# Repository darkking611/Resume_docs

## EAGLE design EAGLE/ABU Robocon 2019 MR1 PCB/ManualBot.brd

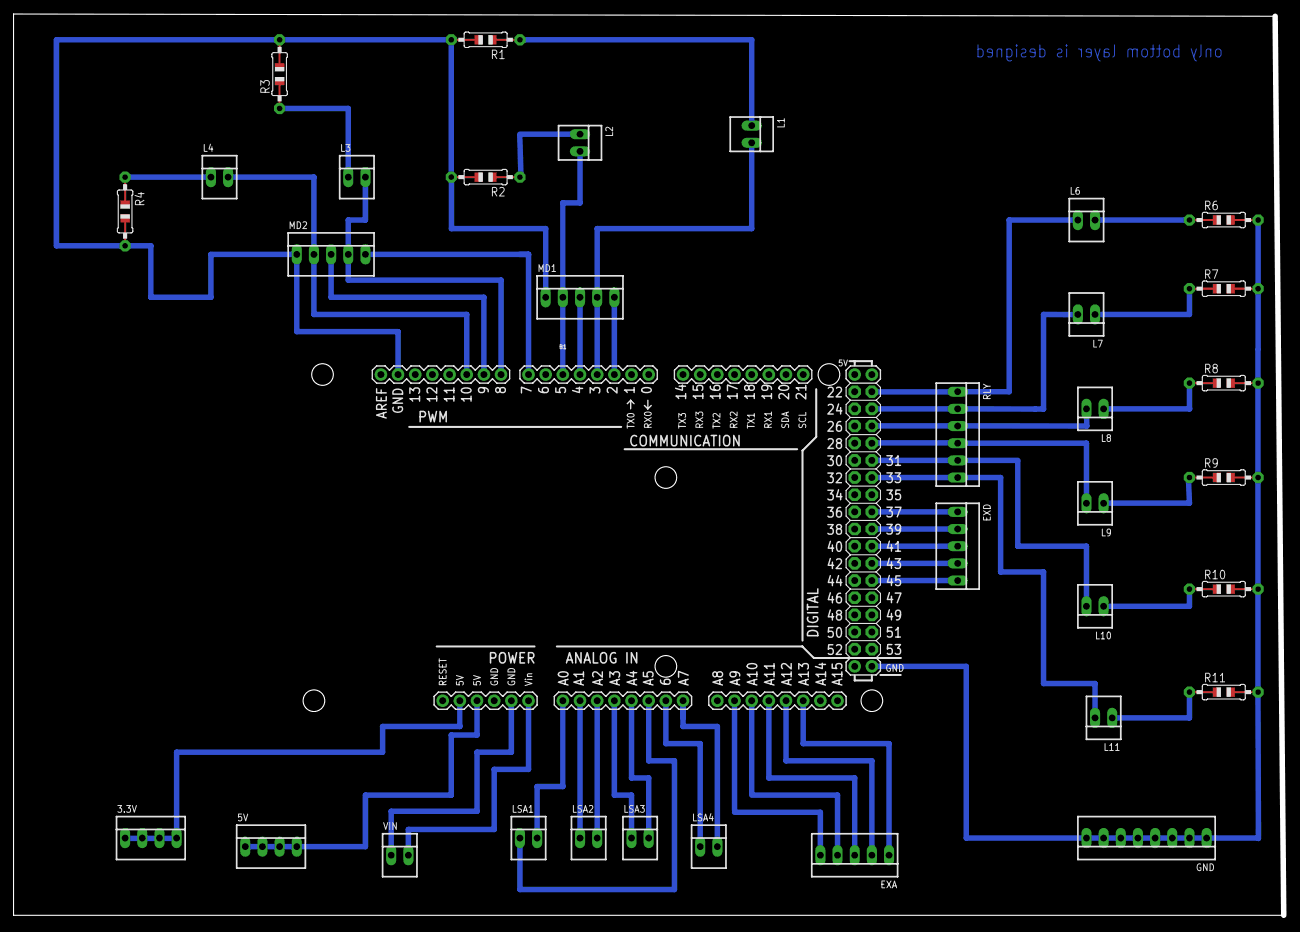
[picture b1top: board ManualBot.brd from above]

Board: 2 copper layers, 187.9 x 133.3 mm, 34 parts (0 on the bottom side), 15 nets.

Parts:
3.3V, 5V: 22-23-2041
B1: ARDUINO_MEGA_R3FULL; ARDUINO_MEGA
EXA: 22-23-2051
EXD: 22-23-2051
GND: 22-23-2081
L1, L2, L3, L4, L6, L7, L8, L9, L10, L11: 22-23-2021
LSA1, LSA2, LSA3, LSA4: 22-23-2021
MD1, MD2: 22-23-2051
R1, R2, R3, R4, R6, R7, R8, R9, R10, R11: 0805-THM
RLY: 22-23-2061
VIN: 22-23-2021

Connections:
B$1: R8.2, R9.2, R10.2, R11.2
unnamed: B1.A7, LSA4.2
unnamed: B1.27, L8.2, RLY.3
unnamed: L9.1, R9.1
unnamed: L11.1, R11.1
unnamed: B1.25, L7.2, RLY.2
unnamed: B1.29, RLY.4
S$9: B1.A1, LSA2.1
S$12: B1.A6, LSA4.1
S$13: B1.A3, LSA3.1
S$14: B1.A5, LSA1.1
S$20: B1.45, EXD.5
S$22: B1.23, RLY.1
S$49: L1.1, R1.1
S$62: 3.3V.1, 3.3V.2, 3.3V.3, 3.3V.4

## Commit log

2019-08-20 Done

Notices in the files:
parts and their libraries:
SparkFun-Boards: Licensing: Creative Commons ShareAlike 4.0 International - https://creativecommons.org/licenses/by-sa/4.0
